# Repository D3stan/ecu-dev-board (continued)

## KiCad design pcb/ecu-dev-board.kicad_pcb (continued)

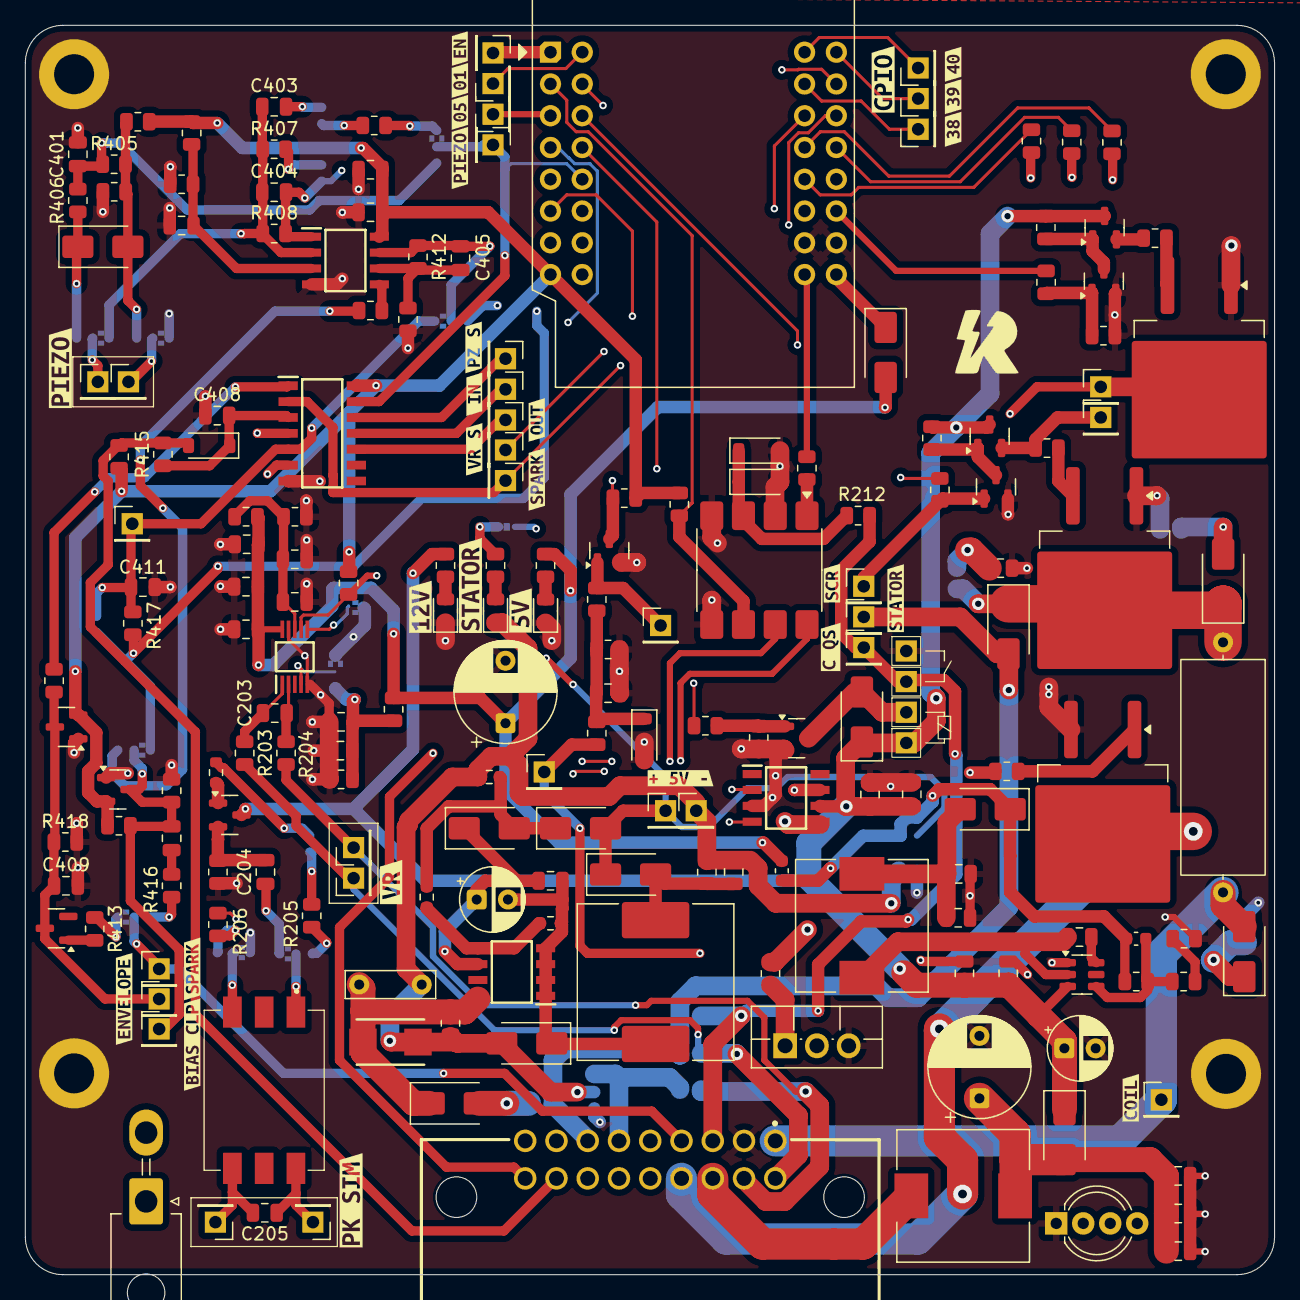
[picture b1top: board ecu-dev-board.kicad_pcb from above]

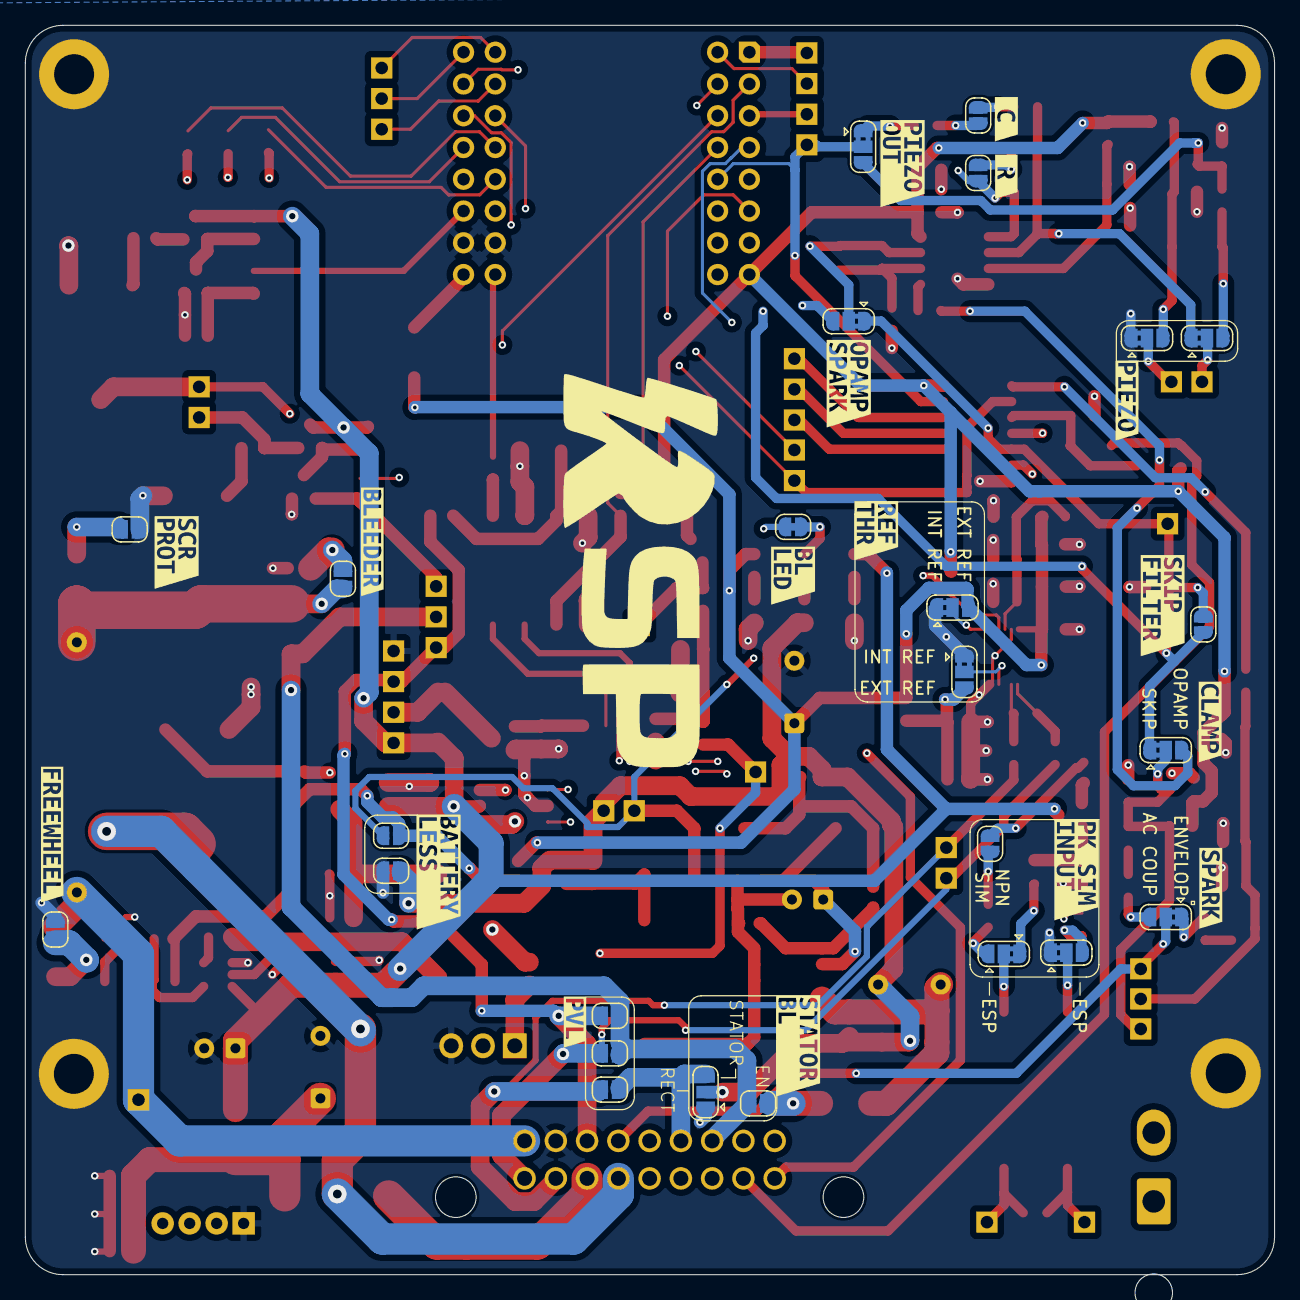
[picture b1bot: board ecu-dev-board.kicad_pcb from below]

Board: 4 copper layers, 99.9 x 99.9 mm, 263 parts (42 on the bottom side), 133 nets.

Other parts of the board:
D1: SS54; D_SMA
kibuzzard-68DC3BCE: G***; kibuzzard-68DC3BCE
kibuzzard-68DC3C5F: G***; kibuzzard-68DC3C5F
kibuzzard-68DC3C6B: G***; kibuzzard-68DC3C6B
kibuzzard-68DC3C7A: G***; kibuzzard-68DC3C7A
kibuzzard-68DC3E65: G***; kibuzzard-68DC3E65
kibuzzard-68DC356E: G***; kibuzzard-68DC356E
kibuzzard-68DD7CEF: G***; kibuzzard-68DD7CEF
kibuzzard-68DD858B: G***; kibuzzard-68DD858B
kibuzzard-68E56D60: G***; kibuzzard-68E56D60
kibuzzard-68E56FCB: G***; kibuzzard-68E56FCB
kibuzzard-68E56FD6: G***; kibuzzard-68E56FD6
kibuzzard-68E57BA0: G***; kibuzzard-68E57BA0
kibuzzard-68E57C5B: G***; kibuzzard-68E57C5B
kibuzzard-68E57F36: G***; kibuzzard-68E57F36
kibuzzard-68E573FB: G***; kibuzzard-68E573FB
kibuzzard-68E576A7: G***; kibuzzard-68E576A7
kibuzzard-68E576ED: G***; kibuzzard-68E576ED
kibuzzard-68E576F3: G***; kibuzzard-68E576F3
kibuzzard-68E577C0: G***; kibuzzard-68E577C0
kibuzzard-68E577E7: G***; kibuzzard-68E577E7
kibuzzard-68E580F6: G***; kibuzzard-68E580F6
kibuzzard-68E57016: G***; kibuzzard-68E57016
kibuzzard-68E57081: G***; kibuzzard-68E57081
kibuzzard-68E57197: G***; kibuzzard-68E57197
kibuzzard-68E57368: G***; kibuzzard-68E57368
kibuzzard-68E57507: G***; kibuzzard-68E57507
kibuzzard-68E57739: G***; kibuzzard-68E57739
kibuzzard-68E57776: G***; kibuzzard-68E57776
kibuzzard-68E57798: G***; kibuzzard-68E57798
kibuzzard-68EB72B9: G***; kibuzzard-68EB72B9
kibuzzard-68EB72C7: G***; kibuzzard-68EB72C7
kibuzzard-68EB72CC: G***; kibuzzard-68EB72CC
kibuzzard-68EB72E2: G***; kibuzzard-68EB72E2
kibuzzard-68EB72EA: G***; kibuzzard-68EB72EA
kibuzzard-68EB72EE: G***; kibuzzard-68EB72EE
kibuzzard-68EB72F2: G***; kibuzzard-68EB72F2
kibuzzard-68EB73A6: G***; kibuzzard-68EB73A6
kibuzzard-68EB732B: G***; kibuzzard-68EB732B
kibuzzard-68EB733C: G***; kibuzzard-68EB733C
kibuzzard-68EB7325: G***; kibuzzard-68EB7325
kibuzzard-68EB7336: G***; kibuzzard-68EB7336
kibuzzard-68EB7341: G***; kibuzzard-68EB7341
kibuzzard-68EB7408: G***; kibuzzard-68EB7408
kibuzzard-68EB7423: G***; kibuzzard-68EB7423

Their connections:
+5V: D1.2 (A); also elsewhere on the board

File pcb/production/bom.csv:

Designator,Footprint,Quantity,Value,LCSC Part #
"C201, C206, C613",0805,3,10u,
"C202, C204, C205, C207, C209, C406, C408, C604, C605, C609, C611, C615, C702",0805,13,100n,
C203,0805,1,1n,
"C208, C409",0805,2,10n,
"C210, C407, C614, C701",0805,4,1u,
C401,0805,1,47n,
C402,0805,1,4u7,
"C403, C404",0805,2,22n,
C405,0805,1,22p,
C410,0805,1,2n2,
C411,0805,1,4n7,
C501,C_Axial_L17.0mm_D6.5mm_P20.00mm_Horizontal,1,1u33,
"C603, C606, C608",0805,3,22u,
C610,0603,1,100p,
C703,0805,1,33n,
"D1, D603, D606, D609",D_SMA,4,SS54,
"D201, D403",D_SOD-123,2,1N4148W,
D401,D_SMA,1,SMAJ20CA,
D402,SOT-23,1,BAT54,
"D404, D405",SOT-23,2,BAT54S,
"D501, D504",TO-263-2,2,TN1215-800G-TR,
"D502, D503, D505, D506, D602, D604, D605, D607",D_SMA,8,US1M,
D601,DIONM5436X261N,1,SMBJ400CA,
"D608, D610",0805,2,RED,
D611,0805,1,GREEN,
FB601,0603,1,BLM18PG121SN1D,
IC201,SOP50P490X110-10N,1,MAX9924UAUB+,
IC401,SOIC127P600X175-14N,1,"74HC14D-Q100,118",
IC601,SOIC127P600X175-8N,1,UCC28910DR,
IC701,SOIC127P600X175-8N,1,UCC27624DR,
J101,MX23A18NF1,1,MX23A18NF1,
J102,Molex_Mini-Fit_Jr_5569-02A2_2x01_P4.20mm_Horizontal,1,39-30-1020,
K501,Ext_Relay,1,Relay,
"L601, L603",L_10.4x10.4_H4.8,2,15u,
L602,L_SXN_SMDRI127,1,150u,
"Q201, Q501, Q503, Q505",SOT-23,4,MMBT2222A,
"Q502, Q504",SOT-23,2,MMBTA55,
Q702,TO-263-2,1,STGB20M65DF2,
Q703,SOT-23,1,AO3400A,
"R201, R202, R203, R204, R208, R209, R210, R211, R401, R402, R403, R404, R406, R410, R411, R414, R417, R421, R506, R603, R702, R704, R706",0805,23,10k,
"R205, R206",0805,2,100R,
R207,0603,1,270,
"R212, R418",0805,2,470k,
"R213, R501, R505",0805,3,470,
"R214, R413, R416, R503",0805,4,47k,
"R301, R302, R303",0805,3,200,
"R405, R407, R408, R419, R510, R601",0805,6,1M,
"R409, R415, R508, R610",0805,4,1k,
R412,0805,1,200k,
R420,0805,1,220k,
"R502, R509, R602",0805,3,100k,
"R504, R507, R611",0805,3,220,
R604,0805,1,3k3,
"R605, R608",0603,2,330k,
R606,0603,1,75k,
R607,0805,1,20k,
R609,0805,1,300,
R701,0805,1,100,
R703,0805,1,3k,
R705,0805,1,10,
T201,SMLP5001E,1,SM-LP-5001E,
U201,SOP-8_6.605x9.655mm_P2.54mm,1,AT223-CuH-S,
U301,WEMOS_S2_mini,1,WeMos_S2_mini,
U401,SOIC127P600X175-8N,1,OPA2376AIDR,
U601,SOT-23-6,1,TPS54202DDC,
"Z201, Z701",D_SOD-123,2,BZT52C4V7,

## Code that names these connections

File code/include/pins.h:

#pragma once
#include <Arduino.h>

// LED Pins
// consteval uint8_t LED_BUILTIN_PIN = 2;
consteval uint8_t R_LED = 21;
consteval uint8_t G_LED = 33;
consteval uint8_t B_LED = 34;

// Pickup Pins
consteval uint8_t PICKUP_SIM_P = 17;
consteval uint8_t PICKUP_SIM_N = 18;
consteval uint8_t PICKUP_SQUARE = 2;

// Quickshift Pins
consteval uint8_t QS_SSR = 15;
consteval uint8_t QS_SCR = 16;
consteval uint8_t QS_TCI = 35;
consteval uint8_t QS_RELAY = 6;

// Spark Pins
consteval uint8_t SPARK_TCI = 37;
consteval uint8_t SPARK_CDI_SSR = 3;

// Actuator Pins
consteval uint8_t POWERJET = 36;
consteval uint8_t CDI = 4;
consteval uint8_t RELAY_PIN = 27;

// Sensor Pins
consteval uint8_t TSP = 7;
consteval uint8_t MAP_SW = 14;

consteval uint8_t PIEZO = 8;
consteval uint8_t PIEZO_SCHMITT = 10;

consteval uint8_t QS_SW = 9;
consteval uint8_t QS_ENABLE = 13;

consteval uint8_t SPARK_TCI = 37;
consteval uint8_t SPARK_CDI_SSR = 3;
consteval uint8_t SPARK_CDI = 11;
consteval uint8_t SPARK_CDI_AC = 12;

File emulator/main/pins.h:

// pins.h - Centralized Pin Assignments
#pragma once

#include "sdkconfig.h"

#if CONFIG_IDF_TARGET_ESP32S2
#define SIM_PIN_PICKUP      13    // Pick-up Coil Pulse Output (LEDC)
#define SIM_PIN_TPS_OUT     16    // TPS Simulated Analog Output (PWM + external RC filter on ESP32-S2)
#define SIM_PIN_EGT_OUT     17    // EGT Simulated Analog Output (DAC Channel 1 / GPIO 17 on ESP32-S2)
#define SIM_PIN_SPARK       21    // CDI Spark Input (GPIO Interrupt)
#define SIM_PIN_QS_OUT      12    // Quick-Shifter digital pulse output (Active-Low)
#define SIM_PIN_QS_IN       14    // Physical Quick-Shifter button input (Active-Low)

#define SIM_PIN_TPS_POT     1     // Physical TPS Potentiometer Input (ADC1_CH0)
#define SIM_PIN_EGT_POT     2     // Physical EGT Potentiometer Input (ADC1_CH1)
#else
// Default/Standard ESP32 pin definitions, avoiding pin conflict on GPIO 25
#define SIM_PIN_PICKUP      4     // Pick-up Coil Pulse Output (LEDC)
#define SIM_PIN_TPS_OUT     26    // TPS Simulated Analog Output (DAC Channel 2 / GPIO 26 on ESP32)
#define SIM_PIN_EGT_OUT     25    // EGT Simulated Analog Output (DAC Channel 1 / GPIO 25 on ESP32)
#define SIM_PIN_SPARK       34    // CDI Spark Input (GPIO Interrupt)
#define SIM_PIN_QS_OUT      12    // Quick-Shifter digital pulse output (Active-Low)
#define SIM_PIN_QS_IN       13    // Physical Quick-Shifter button input (Active-Low)

#define SIM_PIN_TPS_POT     32    // Physical TPS Potentiometer Input (ADC1)
#define SIM_PIN_EGT_POT     33    // Physical EGT Potentiometer Input (ADC1)
#endif

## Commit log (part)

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2025-08-30 added pickupsim section
2025-08-30 added pickupsim section 1
2025-08-30 added footprints to pickup sim
2025-08-30 created MCU sheet
2025-08-30 created MCU sheet 1
2025-08-30 added VR input IC conditioner
2025-08-30 added mode selection
2025-08-30 finetuining
2025-08-31 added SSR
2025-08-31 added CDI
2025-08-31 small fix
2025-09-01 added spark detection
2025-09-01 added batteryless function
2025-09-01 minor corrections
2025-09-01 added production folder for semplicity
2025-09-01 added predisposition for second piezo conditioning circuit
2025-09-04 video call revision
2025-09-05 added 12 to 5 buck
2025-09-05 added reverse polarity protection
2025-09-05 added TCI quickshifter file
2025-09-05 implemented TCI quickshifter
2025-09-05 fixed IGBT logic
2025-09-05 added footprints
2025-09-15 added SCR from kill switch to GND and RGB led
2025-09-15 added digital input for QS
2025-09-15 fixed basic pcb errors
2025-09-16 added connector and simulation link
2025-09-16 added more connector tags
2025-09-16 enhanced pickup simulation
2025-09-16 changed capacitors and resistors footprints from 0201 to 0603
2025-09-17 changed SCR drives to pnp drive and started schematic revision
2025-09-17 removed mode A1 from MAX9924 configuration
2025-09-17 simplified pickup simulation pinout
2025-09-20 completed photomos revision
2025-09-20 changed the QS cut to use a relay
2025-09-20 fixed reverse polarity protection
2025-09-20 added proper handling and comments to QS digital sensor
2025-09-22 changed R and C to standard values
2025-09-22 added more stable output feedback to the ACDC converter
2025-09-22 enhanced spark detection circuit
2025-09-23 improved opamp charge amplifier
2025-09-23 widely changed TCI schematic to use a FET IC driver
2025-09-23 removed small schematic error
2025-09-23 change some resistor footprints to 0.25W compatible
2025-09-23 added more test points
2025-09-23 added PSU status LEDs and stator winding support
2025-09-23 fixed LEDs footprints
2025-09-23 fixed pcb import errors
2025-09-23 added custom footprint for external relay
2025-09-23 changed photomos footprint to match datasheet
2025-09-23 updated inductance footprints
2025-09-24 added DNP for fabrication and 2P molex connector, minor fixes
2025-09-24 added 3D models for connectors and MCU
2025-09-24 initiated PCB modelling
2025-09-25 added another CDI output sensing (opto coupler)
2025-09-25 changed to THT footprint for better analysis
2025-09-25 removed unnecessary jumpers
2025-09-25 made some re-routing to reduce EMI
2025-09-25 added pull-downs to QS stuff
2025-09-25 MCU labels rework
2025-09-25 removed GNDPWR
2025-09-25 added schottky OR-ing to DC converters
2025-09-25 moved the bulk cap outside
2025-09-25 more minor fixes
2025-09-25 changed zener footprints
2025-09-25 added PVL ignitions support
2025-09-25 added notes
2025-09-25 changed THT to SMD for both resistors and capacitors since they will be replaced by hand with soldering tweezers
2025-09-25 updated SCRs footprint
2025-09-25 added ideal maximum board size
2025-09-25 organized pcb
2025-09-25 ordered jumpers and test pins
2025-09-26 revision 2.0: added LC Vbatt filtering and changed Pmos protection to be a schttoky
2025-09-26 revision 2.0: changed components numeration
2025-09-26 revision 2.0: changed R and C footprints to 0805 (imperial)
2025-09-26 revision 2.0: other minor changed
2025-09-27 revision 2.0: changed 47uF footprint
2025-09-27 pcb first iteration of power implementation
2025-09-27 moved ac-dc converter
2025-09-29 placed CDI components
2025-09-29 removed duplicated test points
2025-09-29 started analogue and signal digital part
2025-09-30 VR conditioning placement
2025-09-30 finished pickup and MCU sheets
2025-09-30 completed PSU sheet
2025-09-30 rounded PCB edges and modified color
2025-09-30 completed TCI sheet placement
2025-10-01 placed all components inside the boards
2025-10-07 added labels
2025-10-07 fixed main connector not positioned
2025-10-07 small cap value
2025-10-08 changed battery pin with coil qs
2025-10-08 routed 12V
2025-10-08 routed 3V3
2025-10-08 power aux connections
2025-10-08 routed batteryless from statort
2025-10-08 routed stator and CDI
2025-10-08 made some traces bigger and routed partially the TCI
2025-10-08 added bigger vias
2025-10-09 started components grounding using vias
2025-10-09 completed components grounding using vias
2025-10-09 routed OPAMP and Schmitt Trigger
2025-10-09 routed GPIOs
2025-10-09 fixed DRC errors
2025-10-09 components updates
2025-10-09 minor fixes
2025-10-12 swapped ADC with digital pins
2025-10-13 removed unnecessary silkscreen designators
2025-10-13 modified pickup sim jumpers
2025-10-13 modified VR conditioner jumpers
2025-10-13 modified BL led jumper
2025-10-13 modified sensors jumpers
2025-10-14 added logos
2025-10-14 added diode to prevent backfeed from USB VBUS to 5V
2025-10-14 moved holes
2025-10-15 added GND planes
2025-10-21 initializated PIO
2025-10-21 refactored .gitignores
2025-10-28 pin mapping
2025-10-28 renamed
2025-10-29 board test: RGB led and pickup simulator
2025-10-29 extracted pickup fun
2025-10-30 board test: PIEZO bench and static bike test
2025-11-16 end phase 1
2025-11-17 created first enclosure
2025-11-17 removed large pcb 3D model
2025-11-17 improved 3D model
2025-11-17 added logo to 3D model
2025-12-03 3d models
2025-12-04 added testing comments
2025-12-09 wrote final tests
2025-12-09 test bench
2025-12-09 first iteration
2025-12-09 mDNS
2025-12-09 fw and fs update
2025-12-09 static json
2025-12-09 added telemetry
2025-12-09 live telemetry
2025-12-10 added dashboard
2025-12-10 working telemetry page
2025-12-10 fixed dashboard
2025-12-10 removed captive portal
2025-12-10 fixed connection
2025-12-10 fixed
2025-12-10 refactored
2025-12-10 enhanced fronted
2025-12-10 added simulation and enhanced qs config
2025-12-10 tooltip handling
2025-12-10 fixed tooltip box
2025-12-10 added scale to graph
2025-12-10 added apple full screen coantent
2025-12-10 centered warning
2025-12-10 tried other fixes
2025-12-10 solved printf crashes
2025-12-10 enhanced network config saving
2025-12-11 ota tries
2025-12-11 manual OTA working, remote not
2025-12-11 added realease mode build
2025-12-11 added rpm filtering
2025-12-11 added mode debugging
2025-12-11 ehnanced dashboard rpm validation
2025-12-12 added manual shift bypass
2026-02-08 updated min debounce
2026-05-27 added idf conf
2026-05-27 added git ignore
2026-05-27 created idf project
2026-05-27 added specs for iot project
2026-05-27 added main ecu doc file
2026-05-28 revisioned specs
2026-05-28 translated specs
2026-05-28 added webui and converted domain
2026-05-28 added implementation plan
2026-05-28 added sim docs
2026-05-29 enhanced simulator documentation
2026-05-29 removed ESPAsyncWebserver dep
2026-05-29 added sim impl plan
2026-05-29 created emulator project
2026-06-07 added first sim implementation
2026-06-07 fixed build errors
2026-06-07 added webui
2026-06-07 added AP initialization
2026-06-08 updated for cross-plat functioning
2026-06-08 fixed web builder
2026-06-08 fixed dashboard but still buggy
2026-06-08 webui from scratch
2026-06-08 implemented first iteration of the webui
2026-06-09 connected backend to fronted
2026-06-09 first idf architecture iteration
2026-06-10 added esp32-s2 pins
2026-06-10 added pins description
2026-06-10 changed pins and IO
2026-06-11 tried fixing ws and adc
2026-06-11 working adc (tps, not egt)
2026-06-11 testing egt emulation
2026-06-11 fixed egt reading, added ws logging
2026-06-12 added GPIO18 problem
2026-06-12 pivoted from DAC to PWM for TPS
2026-06-12 docs: normalize callouts to portable blockquotes and fix file:/// links in implementation_plan.md
2026-06-12 docs: normalize 4 GitHub-style callouts to portable > **Important:** / **Warning:** / **Note:** in elaborato.md
2026-06-12 docs: normalize callout and file:/// links to portable relative in sim/sim_implementation_plan.md
2026-06-12 docs: fix relative links in sim/architecture.md (mermaid diagram already valid portable syntax)
2026-06-12 docs: fix 6 class diagrams (C++ ~ types->aliases e.g. BreakpointArray, span~->Span, <<POD / trivially...>> -> <<trivially_copyable>>, remove $ on handlers), convert 5 callouts, fix top file:/// links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
2026-06-12 docs: fix 6 classDiagrams + 1 graph in oop_architecture.md (type aliases: BreakpointArray/Span, CharArray16, OptionalEngineEvent, MapSetArray etc; stereotypes <<value_object>> <<trivially_copyable>> 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
2026-06-12 docs: fix last 2 Mermaid diagrams (InputNumber flow -> valid graph TD with quoted labels; webui-conversion phase graph minor), convert 6 callouts in conversion-plan, normalize top links
2026-06-12 docs: add implementation plan per writing-plans skill for the Mermaid+MD normalization work
2026-06-12 removed plan
2026-06-13 added sensors specifications
2026-06-14 small corrections
2026-06-14 removed EGT from timing calculations
2026-06-14 added roadmap
2026-06-14 added sensors OOP design
2026-06-14 completed sensors analysis
2026-06-14 final review
2026-06-14 refactoring
2026-06-14 major refactoring for sensors macro-area
2026-06-14 removed unused docs files
2026-06-14 removed old broken UI
2026-06-14 first implementation of sensors subsystem
2026-06-14 added testing guide
2026-06-15 added first DT specifications
2026-06-15 added esp32s3 specs
2026-06-15 completed docs and added real testing
2026-06-15 updated testing guide
2026-06-15 fixed crash + added manu config
2026-06-15 added mixed emulated sensors support
2026-06-15 docs refactoring
2026-06-15 implemented pickup interrupt
2026-06-15 implemented ADC calibration/scaling for real sensors
2026-06-16 added digital twin design
2026-06-16 enhanced sensors testing, extracted classes from drivers for better PC testing
2026-06-16 refactored emulator code
2026-06-16 updated testing guide and added posix support
2026-06-16 added first doc
2026-06-16 removed old app
2026-06-16 added basic telemetry oop contracts
2026-06-16 implemented telemetry and added web ui
2026-06-16 added webserver doc
2026-06-16 implemented telemetry webserver
2026-06-16 updated webui doc
2026-06-16 renamed file
2026-06-16 added webui websocket remapping
2026-06-16 adapted webui to current websocket telemetry messages
2026-06-16 added ui specs
2026-06-16 revised implementation plans
2026-06-17 run npm audit fix
2026-06-17 added partition scheme and webserver file serving
2026-06-17 added design doc
2026-06-17 fixed webserver crash
2026-06-17 first implementation
2026-06-17 fixed deploy crash
2026-06-17 added DB safeguard for migrations
2026-06-17 added better config for db url
2026-06-17 fixed TimescaleDB's create_hypertable
2026-06-17 debugging DB
2026-06-17 given correct logs
2026-06-17 still debugging
2026-06-17 added Vue frontend
2026-06-17 remapped ports
2026-06-17 updated routing rules
2026-06-17 removed car
2026-06-17 implemented client - server communication
2026-06-17 adapted to new telemetry
2026-06-17 fixed compilation errors
2026-06-17 changed ui style
2026-06-17 fixed crashes
2026-06-17 revised server architecture
2026-06-18 added text
2026-06-19 second iteration
2026-06-20 improved domain introduction
2026-06-20 added actors and requirements sections
2026-06-20 updated cors origin
2026-06-20 fixed dokploy config
2026-06-20 fixed frontend error
2026-06-20 fixed telemetry logs
2026-06-20 implemented remote telemetry
2026-06-21 docs: design firmware version run metadata
2026-06-21 docs: plan firmware version run metadata
2026-06-21 fixed webui interface
2026-06-21 feat: expose firmware version in ECU capabilities
2026-06-21 feat: attach ECU firmware version to recorded runs
2026-06-21 fix: show firmware without engine map metadata
2026-06-21 docs: align firmware plan with merged worktree
2026-06-21 removed unused files
2026-06-21 added git describe to compilation
2026-06-21 removed unnecessary stuff
2026-06-21 added report structure
2026-06-21 fixed mermaid diagram
2026-06-21 sensor acquisition section
2026-06-21 enhanced architecture section
2026-06-21 clarified telemetry section
2026-06-21 enhanced server and client
2026-06-21 modified client section
2026-06-21 better tests explanation
2026-06-21 added conclusions
2026-06-21 grammatical corrections
